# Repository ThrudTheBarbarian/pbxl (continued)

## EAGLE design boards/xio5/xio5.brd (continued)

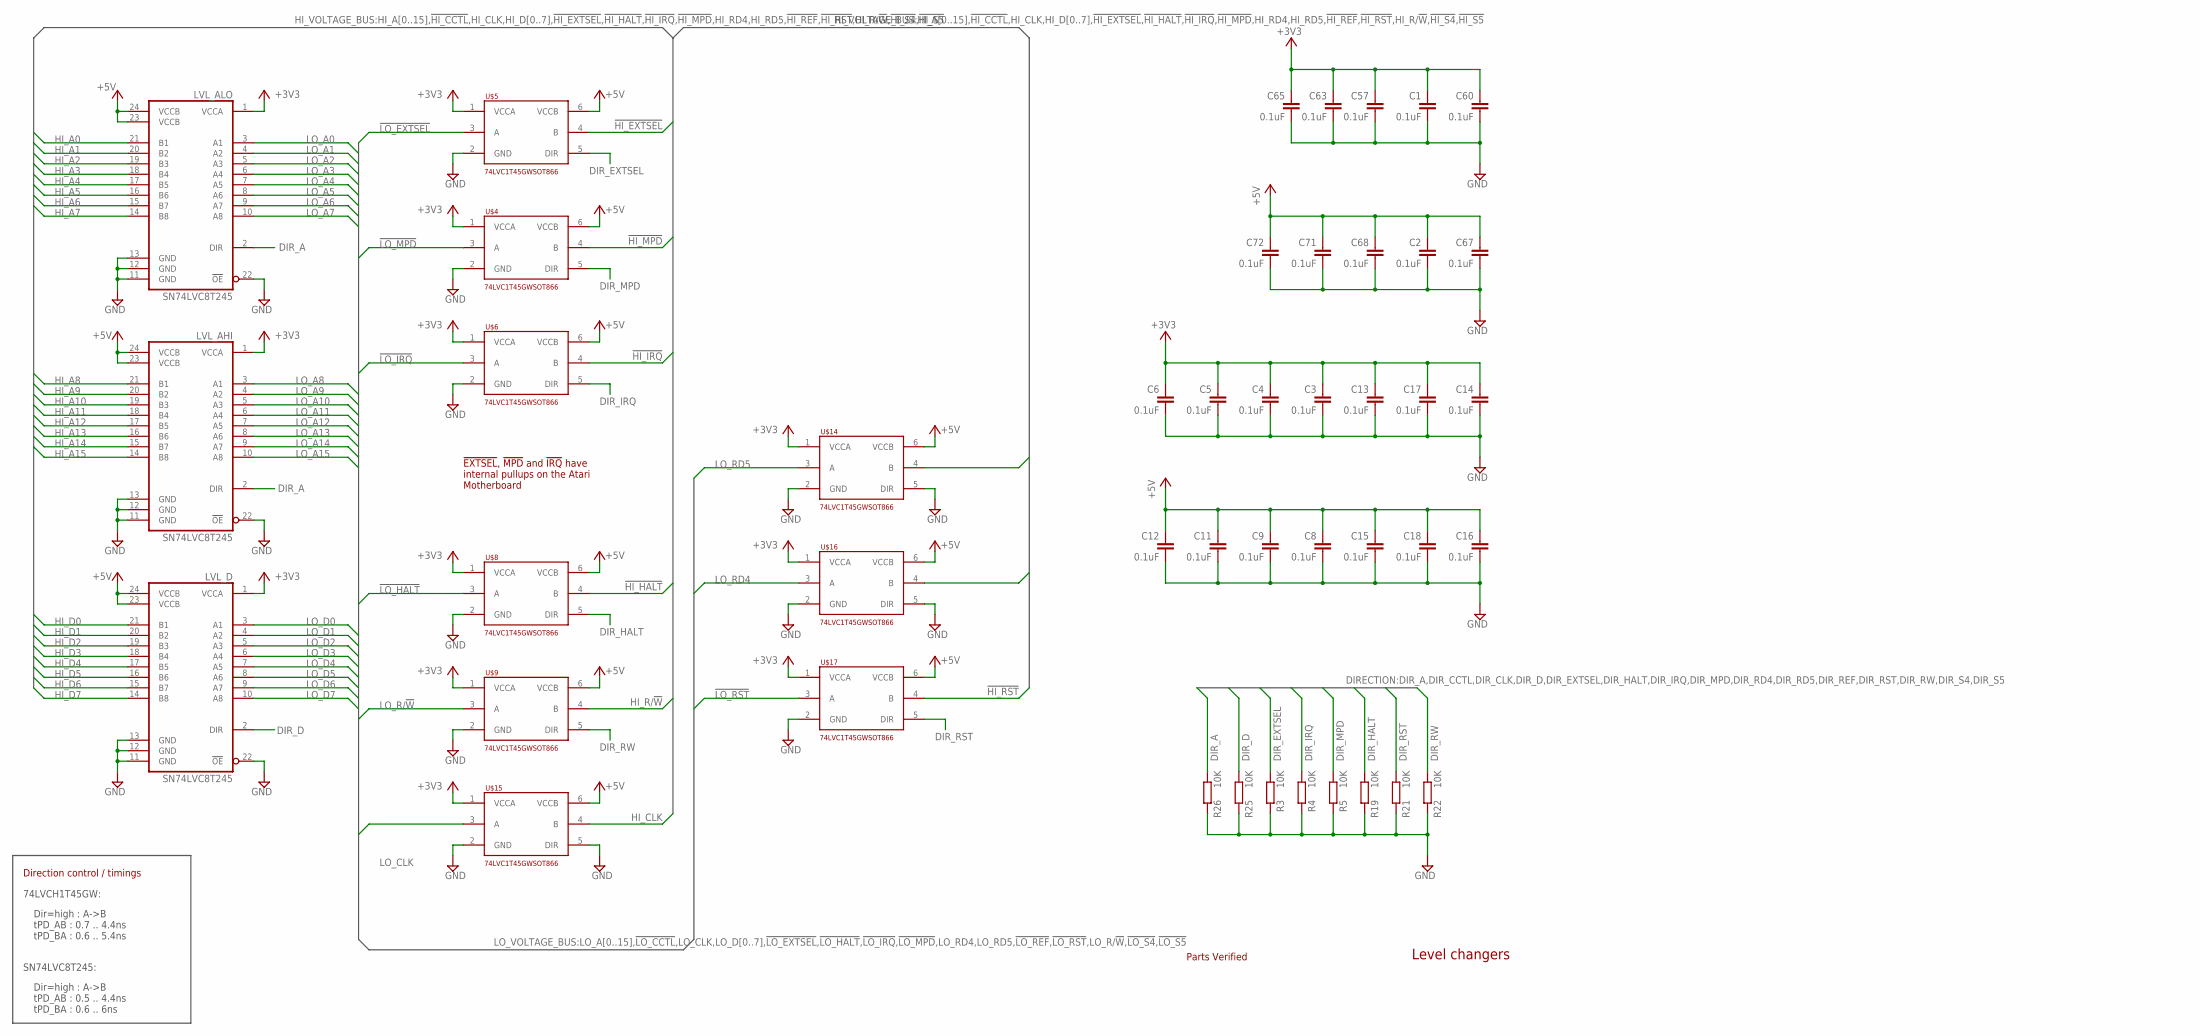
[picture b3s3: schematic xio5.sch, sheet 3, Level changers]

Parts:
C1, C2, C3, C4, C5, C6, C8, C9, C11, C12, C13, C14, C15, C16, C17, C18, C57, C60, C63, C65, C67, C68, C71, C72: 0.1uF; C0201
LVL_AHI: SN74LVC8T245; TSSOP24
LVL_ALO: SN74LVC8T245; TSSOP24
LVL_D: SN74LVC8T245; TSSOP24
R3, R4, R5, R19, R21, R22, R25, R26: 10K; R0201
U$4, U$5, U$6, U$8, U$9, U$14, U$15, U$16, U$17: 74LVC1T45GWSOT866; SOT886

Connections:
!HI_EXTSEL!: U$5.4 (B); also elsewhere on the board
!HI_HALT!: U$8.4 (B); also elsewhere on the board
!HI_IRQ!: U$6.4 (B); also elsewhere on the board
!HI_MPD!: U$4.4 (B); also elsewhere on the board
!HI_RST!: U$17.4 (B); also elsewhere on the board
!LO_EXTSEL!: U$5.3 (A); also elsewhere on the board
!LO_HALT!: U$8.3 (A); also elsewhere on the board
!LO_IRQ!: U$6.3 (A); also elsewhere on the board
!LO_MPD!: U$4.3 (A); also elsewhere on the board
!LO_RST!: U$17.3 (A); also elsewhere on the board
+3V3: C1.1, C3.1, C4.1, C5.1, C6.1, C13.1, C14.1, C17.1, C57.1, C60.1, C63.1, C65.1, LVL_AHI.1 (VCCA), LVL_ALO.1 (VCCA), LVL_D.1 (VCCA), U$4.1 (VCCA), U$5.1 (VCCA), U$6.1 (VCCA), U$8.1 (VCCA), U$9.1 (VCCA), U$14.1 (VCCA), U$15.1 (VCCA), U$16.1 (VCCA), U$17.1 (VCCA); also elsewhere on the board
+5V: C2.1, C8.1, C9.1, C11.1, C12.1, C15.1, C16.1, C18.1, C67.1, C68.1, C71.1, C72.1, LVL_AHI.23 (VCCB), LVL_AHI.24 (VCCB), LVL_ALO.23 (VCCB), LVL_ALO.24 (VCCB), LVL_D.23 (VCCB), LVL_D.24 (VCCB), U$4.6 (VCCB), U$5.6 (VCCB), U$6.6 (VCCB), U$8.6 (VCCB), U$9.6 (VCCB), U$14.6 (VCCB), U$15.6 (VCCB), U$16.6 (VCCB), U$17.6 (VCCB); also elsewhere on the board
DIR_A: LVL_AHI.2 (DIR), LVL_ALO.2 (DIR), R26.1; also elsewhere on the board
DIR_D: LVL_D.2 (DIR), R25.1; also elsewhere on the board
DIR_EXTSEL: R3.1, U$5.5 (DIR); also elsewhere on the board
DIR_HALT: R19.1, U$8.5 (DIR); also elsewhere on the board
DIR_IRQ: R4.1, U$6.5 (DIR); also elsewhere on the board
DIR_MPD: R5.1, U$4.5 (DIR); also elsewhere on the board
DIR_RST: R21.1, U$17.5 (DIR); also elsewhere on the board
DIR_RW: R22.1, U$9.5 (DIR); also elsewhere on the board
GND: C1.2, C2.2, C3.2, C4.2, C5.2, C6.2, C8.2, C9.2, C11.2, C12.2, C13.2, C14.2, C15.2, C16.2, C17.2, C18.2, C57.2, C60.2, C63.2, C65.2, C67.2, C68.2, C71.2, C72.2, LVL_AHI.11 (GND), LVL_AHI.12 (GND), LVL_AHI.13 (GND), LVL_AHI.22 (!OE!), LVL_ALO.11 (GND), LVL_ALO.12 (GND), LVL_ALO.13 (GND), LVL_ALO.22 (!OE!), LVL_D.11 (GND), LVL_D.12 (GND), LVL_D.13 (GND), LVL_D.22 (!OE!), R3.2, R4.2, R5.2, R19.2, R21.2, R22.2, R25.2, R26.2, U$4.2 (GND), U$5.2 (GND), U$6.2 (GND), U$8.2 (GND), U$9.2 (GND), U$14.2 (GND), U$14.5 (DIR), U$15.2 (GND), U$15.5 (DIR), U$16.2 (GND), U$16.5 (DIR), U$17.2 (GND); also elsewhere on the board
HI_A0: LVL_ALO.21 (B1); also elsewhere on the board
HI_A1: LVL_ALO.20 (B2); also elsewhere on the board
HI_A2: LVL_ALO.19 (B3); also elsewhere on the board
HI_A3: LVL_ALO.18 (B4); also elsewhere on the board
HI_A4: LVL_ALO.17 (B5); also elsewhere on the board
HI_A5: LVL_ALO.16 (B6); also elsewhere on the board
HI_A6: LVL_ALO.15 (B7); also elsewhere on the board
HI_A7: LVL_ALO.14 (B8); also elsewhere on the board
HI_A8: LVL_AHI.21 (B1); also elsewhere on the board
HI_A9: LVL_AHI.20 (B2); also elsewhere on the board
HI_A10: LVL_AHI.19 (B3); also elsewhere on the board
HI_A11: LVL_AHI.18 (B4); also elsewhere on the board
HI_A12: LVL_AHI.17 (B5); also elsewhere on the board
HI_A13: LVL_AHI.16 (B6); also elsewhere on the board
HI_A14: LVL_AHI.15 (B7); also elsewhere on the board
HI_A15: LVL_AHI.14 (B8); also elsewhere on the board
HI_CLK: U$15.4 (B); also elsewhere on the board
HI_D0: LVL_D.21 (B1); also elsewhere on the board
HI_D1: LVL_D.20 (B2); also elsewhere on the board
HI_D2: LVL_D.19 (B3); also elsewhere on the board
HI_D3: LVL_D.18 (B4); also elsewhere on the board
HI_D4: LVL_D.17 (B5); also elsewhere on the board
HI_D5: LVL_D.16 (B6); also elsewhere on the board
HI_D6: LVL_D.15 (B7); also elsewhere on the board
HI_D7: LVL_D.14 (B8); also elsewhere on the board
HI_R/!W!: U$9.4 (B); also elsewhere on the board
HI_RD4: U$16.4 (B); also elsewhere on the board
HI_RD5: U$14.4 (B); also elsewhere on the board
LO_A0: LVL_ALO.3 (A1); also elsewhere on the board
LO_A1: LVL_ALO.4 (A2); also elsewhere on the board
LO_A2: LVL_ALO.5 (A3); also elsewhere on the board
LO_A3: LVL_ALO.6 (A4); also elsewhere on the board
LO_A4: LVL_ALO.7 (A5); also elsewhere on the board
LO_A5: LVL_ALO.8 (A6); also elsewhere on the board
LO_A6: LVL_ALO.9 (A7); also elsewhere on the board
LO_A7: LVL_ALO.10 (A8); also elsewhere on the board
LO_A8: LVL_AHI.3 (A1); also elsewhere on the board
LO_A9: LVL_AHI.4 (A2); also elsewhere on the board
LO_A10: LVL_AHI.5 (A3); also elsewhere on the board
LO_A11: LVL_AHI.6 (A4); also elsewhere on the board
LO_A12: LVL_AHI.7 (A5); also elsewhere on the board
LO_A13: LVL_AHI.8 (A6); also elsewhere on the board
LO_A14: LVL_AHI.9 (A7); also elsewhere on the board
LO_A15: LVL_AHI.10 (A8); also elsewhere on the board
LO_CLK: U$15.3 (A); also elsewhere on the board
LO_D0: LVL_D.3 (A1); also elsewhere on the board
LO_D1: LVL_D.4 (A2); also elsewhere on the board
LO_D2: LVL_D.5 (A3); also elsewhere on the board
LO_D3: LVL_D.6 (A4); also elsewhere on the board
LO_D4: LVL_D.7 (A5); also elsewhere on the board
LO_D5: LVL_D.8 (A6); also elsewhere on the board
LO_D6: LVL_D.9 (A7); also elsewhere on the board
LO_D7: LVL_D.10 (A8); also elsewhere on the board
LO_R/!W!: U$9.3 (A); also elsewhere on the board
LO_RD4: U$16.3 (A); also elsewhere on the board
LO_RD5: U$14.3 (A); also elsewhere on the board

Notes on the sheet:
Dir=high : A->B tPD_AB : 0.7 .. 4.4ns tPD_BA : 0.6 .. 5.4ns
74LVCH1T45GW:
SN74LVC8T245:
Dir=high : A->B tPD_AB : 0.5 .. 4.4ns tPD_BA : 0.6 .. 6ns
Direction control / timings
Level changers
!EXTSEL!, !MPD! and !IRQ! have internal pullups on the Atari Motherboard
Parts Verified

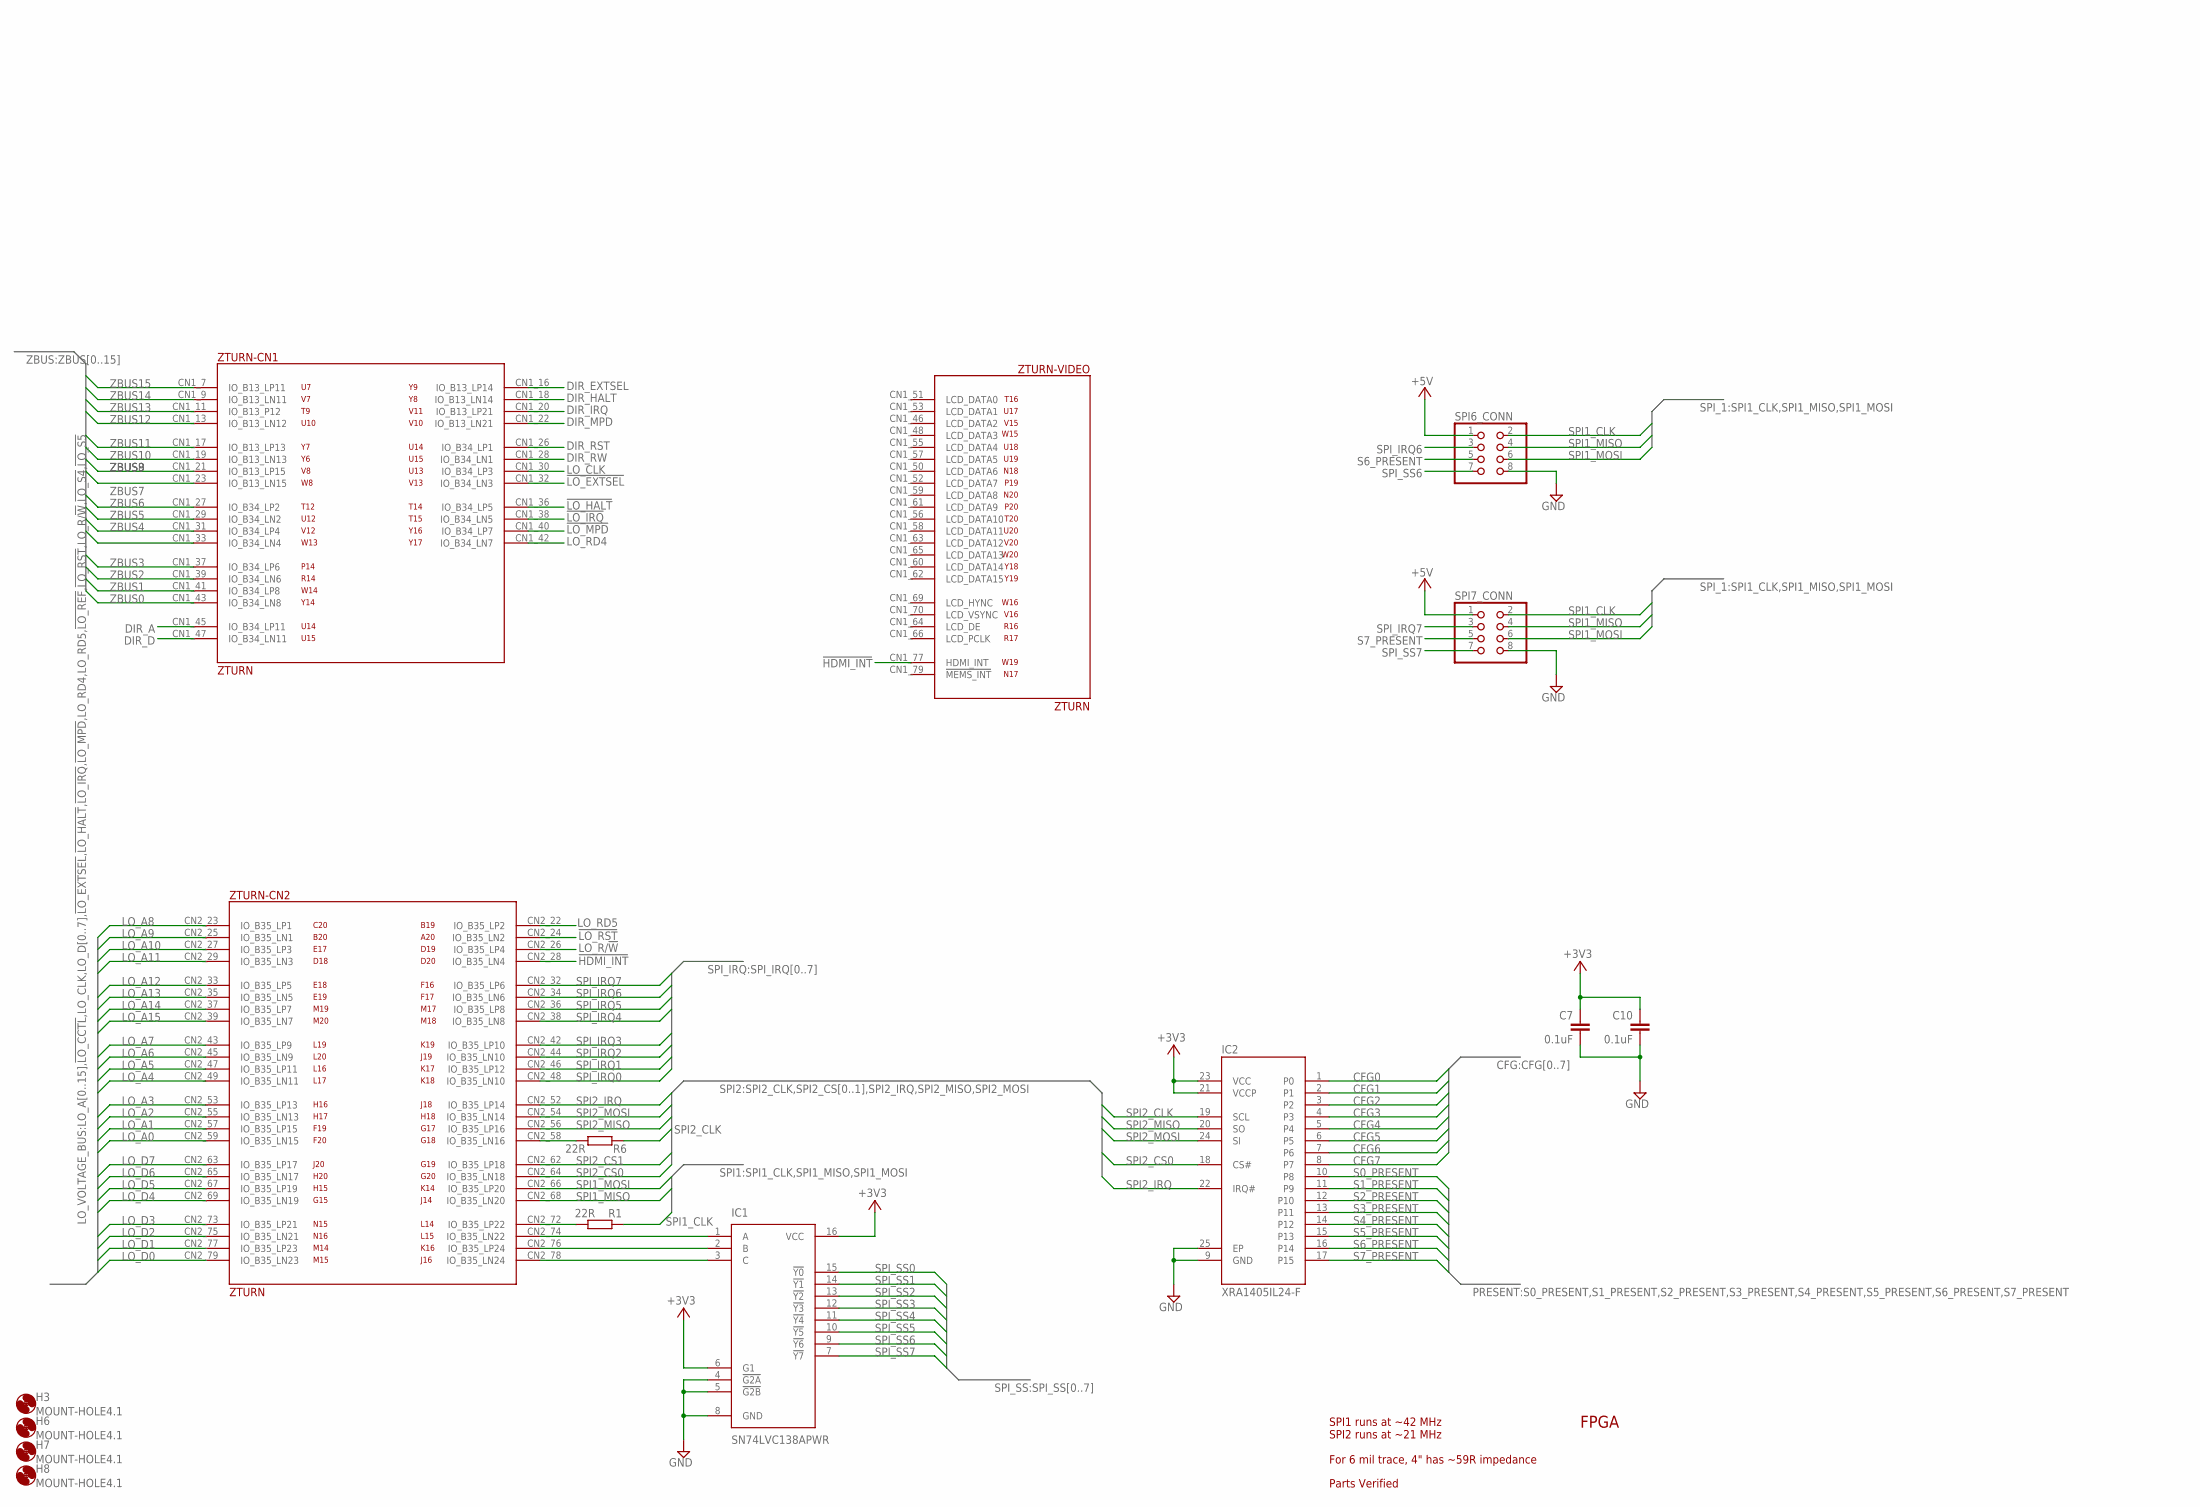
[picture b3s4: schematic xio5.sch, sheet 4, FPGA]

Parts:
C7, C10: 0.1uF; C0201
H3, H6, H7, H8: MOUNT-HOLE4.1; 4,1
IC1: SN74LVC138APWR; SOP65P640X120-16N
IC2: XRA1405IL24-F; QFN50P400X400X100-25N
R1, R6: 22R; R0201
SPI6_CONN, SPI7_CONN: PINHD-2X04_2.00; 2X04M
ZTURN: ZTURN

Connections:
!HDMI_INT!: ZTURN.CN1_77 (HDMI_INT), ZTURN.CN2_28 (IO_B35_LN4)
!LO_EXTSEL!: ZTURN.CN1_32 (IO_B34_LN3); also elsewhere on the board
!LO_HALT!: ZTURN.CN1_36 (IO_B34_LP5); also elsewhere on the board
!LO_IRQ!: ZTURN.CN1_38 (IO_B34_LN5); also elsewhere on the board
!LO_MPD!: ZTURN.CN1_40 (IO_B34_LP7); also elsewhere on the board
!LO_RST!: ZTURN.CN2_24 (IO_B35_LN2); also elsewhere on the board
+3V3: C7.1, C10.1, IC1.6 (G1), IC1.16 (VCC), IC2.21 (VCCP), IC2.23 (VCC); also elsewhere on the board
+5V: SPI6_CONN.1, SPI7_CONN.1; also elsewhere on the board
CFG0: IC2.1 (P0); also elsewhere on the board
CFG1: IC2.2 (P1); also elsewhere on the board
CFG2: IC2.3 (P2); also elsewhere on the board
CFG3: IC2.4 (P3); also elsewhere on the board
CFG4: IC2.5 (P4); also elsewhere on the board
CFG5: IC2.6 (P5); also elsewhere on the board
CFG6: IC2.7 (P6); also elsewhere on the board
CFG7: IC2.8 (P7); also elsewhere on the board
DIR_A: ZTURN.CN1_45 (IO_B34_LP11); also elsewhere on the board
DIR_D: ZTURN.CN1_47 (IO_B34_LN11); also elsewhere on the board
DIR_EXTSEL: ZTURN.CN1_16 (IO_B13_LP14); also elsewhere on the board
DIR_HALT: ZTURN.CN1_18 (IO_B13_LN14); also elsewhere on the board
DIR_IRQ: ZTURN.CN1_20 (IO_B13_LP21); also elsewhere on the board
DIR_MPD: ZTURN.CN1_22 (IO_B13_LN21); also elsewhere on the board
DIR_RST: ZTURN.CN1_26 (IO_B34_LP1); also elsewhere on the board
DIR_RW: ZTURN.CN1_28 (IO_B34_LN1); also elsewhere on the board
GND: C7.2, C10.2, IC1.4 (!G2A), IC1.5 (!G2B), IC1.8 (GND), IC2.9 (GND), IC2.25 (EP), SPI6_CONN.8, SPI7_CONN.8; also elsewhere on the board
LO_A0: ZTURN.CN2_59 (IO_B35_LN15); also elsewhere on the board
LO_A1: ZTURN.CN2_57 (IO_B35_LP15); also elsewhere on the board
LO_A2: ZTURN.CN2_55 (IO_B35_LN13); also elsewhere on the board
LO_A3: ZTURN.CN2_53 (IO_B35_LP13); also elsewhere on the board
LO_A4: ZTURN.CN2_49 (IO_B35_LN11); also elsewhere on the board
LO_A5: ZTURN.CN2_47 (IO_B35_LP11); also elsewhere on the board
LO_A6: ZTURN.CN2_45 (IO_B35_LN9); also elsewhere on the board
LO_A7: ZTURN.CN2_43 (IO_B35_LP9); also elsewhere on the board
LO_A8: ZTURN.CN2_23 (IO_B35_LP1); also elsewhere on the board
LO_A9: ZTURN.CN2_25 (IO_B35_LN1); also elsewhere on the board
LO_A10: ZTURN.CN2_27 (IO_B35_LP3); also elsewhere on the board
LO_A11: ZTURN.CN2_29 (IO_B35_LN3); also elsewhere on the board
LO_A12: ZTURN.CN2_33 (IO_B35_LP5); also elsewhere on the board
LO_A13: ZTURN.CN2_35 (IO_B35_LN5); also elsewhere on the board
LO_A14: ZTURN.CN2_37 (IO_B35_LP7); also elsewhere on the board
LO_A15: ZTURN.CN2_39 (IO_B35_LN7); also elsewhere on the board
LO_CLK: ZTURN.CN1_30 (IO_B34_LP3); also elsewhere on the board
LO_D0: ZTURN.CN2_79 (IO_B35_LN23); also elsewhere on the board
LO_D1: ZTURN.CN2_77 (IO_B35_LP23); also elsewhere on the board
LO_D2: ZTURN.CN2_75 (IO_B35_LN21); also elsewhere on the board
LO_D3: ZTURN.CN2_73 (IO_B35_LP21); also elsewhere on the board
LO_D4: ZTURN.CN2_69 (IO_B35_LN19); also elsewhere on the board
LO_D5: ZTURN.CN2_67 (IO_B35_LP19); also elsewhere on the board
LO_D6: ZTURN.CN2_65 (IO_B35_LN17); also elsewhere on the board
LO_D7: ZTURN.CN2_63 (IO_B35_LP17); also elsewhere on the board
LO_R/!W!: ZTURN.CN2_26 (IO_B35_LP4); also elsewhere on the board
LO_RD4: ZTURN.CN1_42 (IO_B34_LN7); also elsewhere on the board
LO_RD5: ZTURN.CN2_22 (IO_B35_LP2); also elsewhere on the board
unnamed: IC1.1 (A), ZTURN.CN2_74 (IO_B35_LN22)
unnamed: IC1.2 (B), ZTURN.CN2_76 (IO_B35_LP24)
unnamed: IC1.3 (C), ZTURN.CN2_78 (IO_B35_LN24)
unnamed: R1.1, ZTURN.CN2_72 (IO_B35_LP22)
unnamed: R6.1, ZTURN.CN2_58 (IO_B35_LN16)
S0_PRESENT: IC2.10 (P8); also elsewhere on the board
S1_PRESENT: IC2.11 (P9); also elsewhere on the board
S2_PRESENT: IC2.12 (P10); also elsewhere on the board
S3_PRESENT: IC2.13 (P11); also elsewhere on the board
S4_PRESENT: IC2.14 (P12); also elsewhere on the board
S5_PRESENT: IC2.15 (P13); also elsewhere on the board
S6_PRESENT: IC2.16 (P14), SPI6_CONN.5
S7_PRESENT: IC2.17 (P15), SPI7_CONN.5
SPI1_CLK: R1.2, SPI6_CONN.2, SPI7_CONN.2; also elsewhere on the board
SPI1_MISO: SPI6_CONN.4, SPI7_CONN.4, ZTURN.CN2_68 (IO_B35_LN20); also elsewhere on the board
SPI1_MOSI: SPI6_CONN.6, SPI7_CONN.6, ZTURN.CN2_66 (IO_B35_LP20); also elsewhere on the board
SPI2_CLK: IC2.19 (SCL), R6.2; also elsewhere on the board
SPI2_CS0: IC2.18 (CS#), ZTURN.CN2_64 (IO_B35_LN18)
SPI2_CS1: ZTURN.CN2_62 (IO_B35_LP18); also elsewhere on the board
SPI2_IRQ: IC2.22 (IRQ#), ZTURN.CN2_52 (IO_B35_LP14); also elsewhere on the board
SPI2_MISO: IC2.20 (SO), ZTURN.CN2_56 (IO_B35_LP16); also elsewhere on the board
SPI2_MOSI: IC2.24 (SI), ZTURN.CN2_54 (IO_B35_LN14); also elsewhere on the board
SPI_IRQ0: ZTURN.CN2_48 (IO_B35_LN10); also elsewhere on the board
SPI_IRQ1: ZTURN.CN2_46 (IO_B35_LP12); also elsewhere on the board
SPI_IRQ2: ZTURN.CN2_44 (IO_B35_LN10); also elsewhere on the board
SPI_IRQ3: ZTURN.CN2_42 (IO_B35_LP10); also elsewhere on the board
SPI_IRQ4: ZTURN.CN2_38 (IO_B35_LN8); also elsewhere on the board
SPI_IRQ5: ZTURN.CN2_36 (IO_B35_LP8); also elsewhere on the board
SPI_IRQ6: SPI6_CONN.3, ZTURN.CN2_34 (IO_B35_LN6)
SPI_IRQ7: SPI7_CONN.3, ZTURN.CN2_32 (IO_B35_LP6)
SPI_SS0: IC1.15 (!Y0); also elsewhere on the board
SPI_SS1: IC1.14 (!Y1); also elsewhere on the board
SPI_SS2: IC1.13 (!Y2); also elsewhere on the board
SPI_SS3: IC1.12 (!Y3); also elsewhere on the board
SPI_SS4: IC1.11 (!Y4); also elsewhere on the board
SPI_SS5: IC1.10 (!Y5); also elsewhere on the board
SPI_SS6: IC1.9 (!Y6), SPI6_CONN.7
SPI_SS7: IC1.7 (!Y7), SPI7_CONN.7
ZBUS0: ZTURN.CN1_43 (IO_B34_LN8); also elsewhere on the board
ZBUS1: ZTURN.CN1_41 (IO_B34_LP8); also elsewhere on the board
ZBUS2: ZTURN.CN1_39 (IO_B34_LN6); also elsewhere on the board
ZBUS3: ZTURN.CN1_37 (IO_B34_LP6); also elsewhere on the board
ZBUS4: ZTURN.CN1_33 (IO_B34_LN4); also elsewhere on the board
ZBUS5: ZTURN.CN1_31 (IO_B34_LP4); also elsewhere on the board
ZBUS6: ZTURN.CN1_29 (IO_B34_LN2); also elsewhere on the board
ZBUS7: ZTURN.CN1_27 (IO_B34_LP2); also elsewhere on the board
ZBUS8: ZTURN.CN1_23 (IO_B13_LN15); also elsewhere on the board
ZBUS9: ZTURN.CN1_21 (IO_B13_LP15); also elsewhere on the board
ZBUS10: ZTURN.CN1_19 (IO_B13_LN13); also elsewhere on the board
ZBUS11: ZTURN.CN1_17 (IO_B13_LP13); also elsewhere on the board
ZBUS12: ZTURN.CN1_13 (IO_B13_LN12); also elsewhere on the board
ZBUS13: ZTURN.CN1_11 (IO_B13_P12); also elsewhere on the board
ZBUS14: ZTURN.CN1_9 (IO_B13_LN11); also elsewhere on the board
ZBUS15: ZTURN.CN1_7 (IO_B13_LP11); also elsewhere on the board

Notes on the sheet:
FPGA
SPI1 runs at ~42 MHz SPI2 runs at ~21 MHz For 6 mil trace, 4" has ~59R impedance
Parts Verified

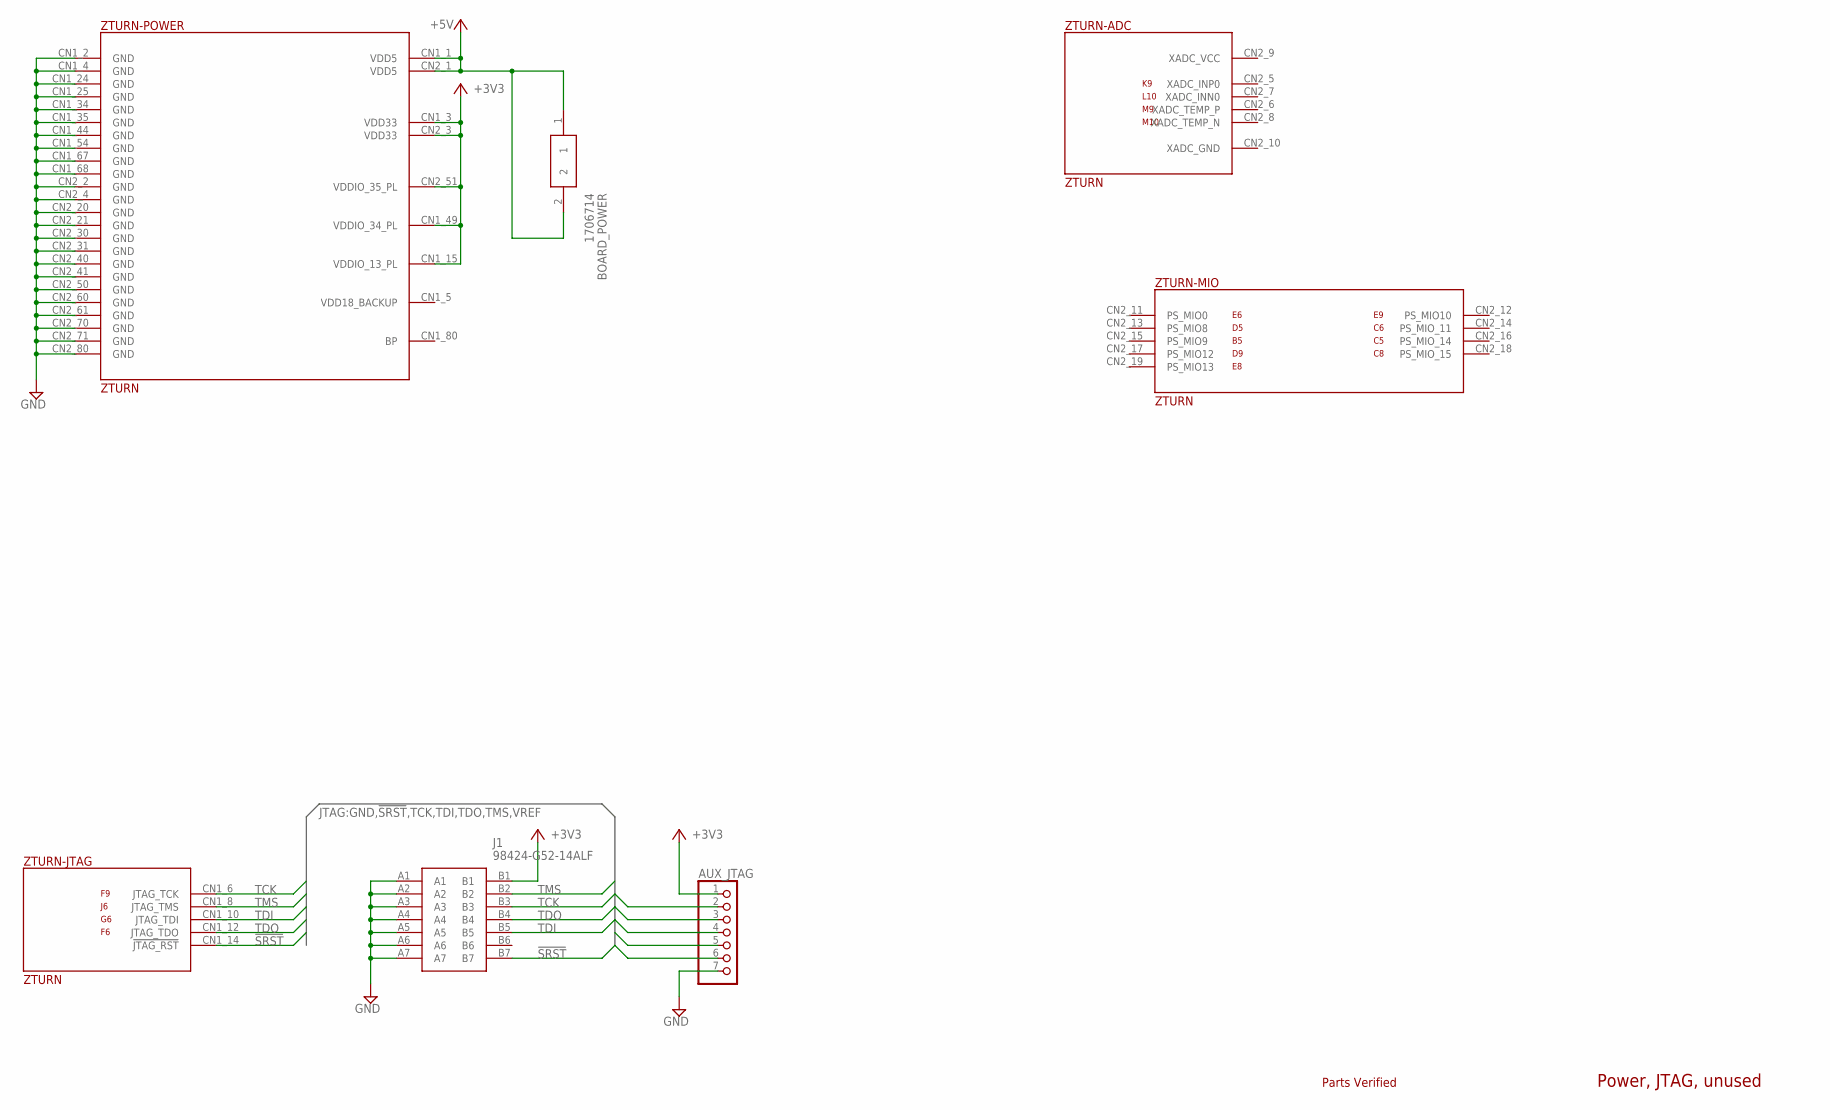
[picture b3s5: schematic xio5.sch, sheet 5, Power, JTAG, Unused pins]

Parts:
AUX_JTAG: PINHD-1X7; 1X07
BOARD_POWER: 1706714
J1: 98424-G52-14ALF; 98424G5214ALF
ZTURN: ZTURN

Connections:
!SRST!: AUX_JTAG.6, J1.B7, ZTURN.CN1_14 (!JTAG_RST!)
+3V3: AUX_JTAG.1, J1.B1, ZTURN.CN1_3 (VDD33), ZTURN.CN1_15 (VDDIO_13_PL), ZTURN.CN1_49 (VDDIO_34_PL), ZTURN.CN2_3 (VDD33), ZTURN.CN2_51 (VDDIO_35_PL); also elsewhere on the board
+5V: BOARD_POWER.1, BOARD_POWER.2, ZTURN.CN1_1 (VDD5), ZTURN.CN2_1 (VDD5); also elsewhere on the board
GND: AUX_JTAG.7, J1.A1, J1.A2, J1.A3, J1.A4, J1.A5, J1.A6, J1.A7, ZTURN.CN1_2 (GND), ZTURN.CN1_4 (GND), ZTURN.CN1_24 (GND), ZTURN.CN1_25 (GND), ZTURN.CN1_34 (GND), ZTURN.CN1_35 (GND), ZTURN.CN1_44 (GND), ZTURN.CN1_54 (GND), ZTURN.CN1_67 (GND), ZTURN.CN1_68 (GND), ZTURN.CN2_2 (GND), ZTURN.CN2_4 (GND), ZTURN.CN2_20 (GND), ZTURN.CN2_21 (GND), ZTURN.CN2_30 (GND), ZTURN.CN2_31 (GND), ZTURN.CN2_40 (GND), ZTURN.CN2_41 (GND), ZTURN.CN2_50 (GND), ZTURN.CN2_60 (GND), ZTURN.CN2_61 (GND), ZTURN.CN2_70 (GND), ZTURN.CN2_71 (GND), ZTURN.CN2_80 (GND); also elsewhere on the board
TCK: AUX_JTAG.3, J1.B3, ZTURN.CN1_6 (JTAG_TCK)
TDI: AUX_JTAG.5, J1.B5, ZTURN.CN1_10 (JTAG_TDI)
TDO: AUX_JTAG.4, J1.B4, ZTURN.CN1_12 (JTAG_TDO)
TMS: AUX_JTAG.2, J1.B2, ZTURN.CN1_8 (JTAG_TMS)

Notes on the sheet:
Power, JTAG, unused
Parts Verified

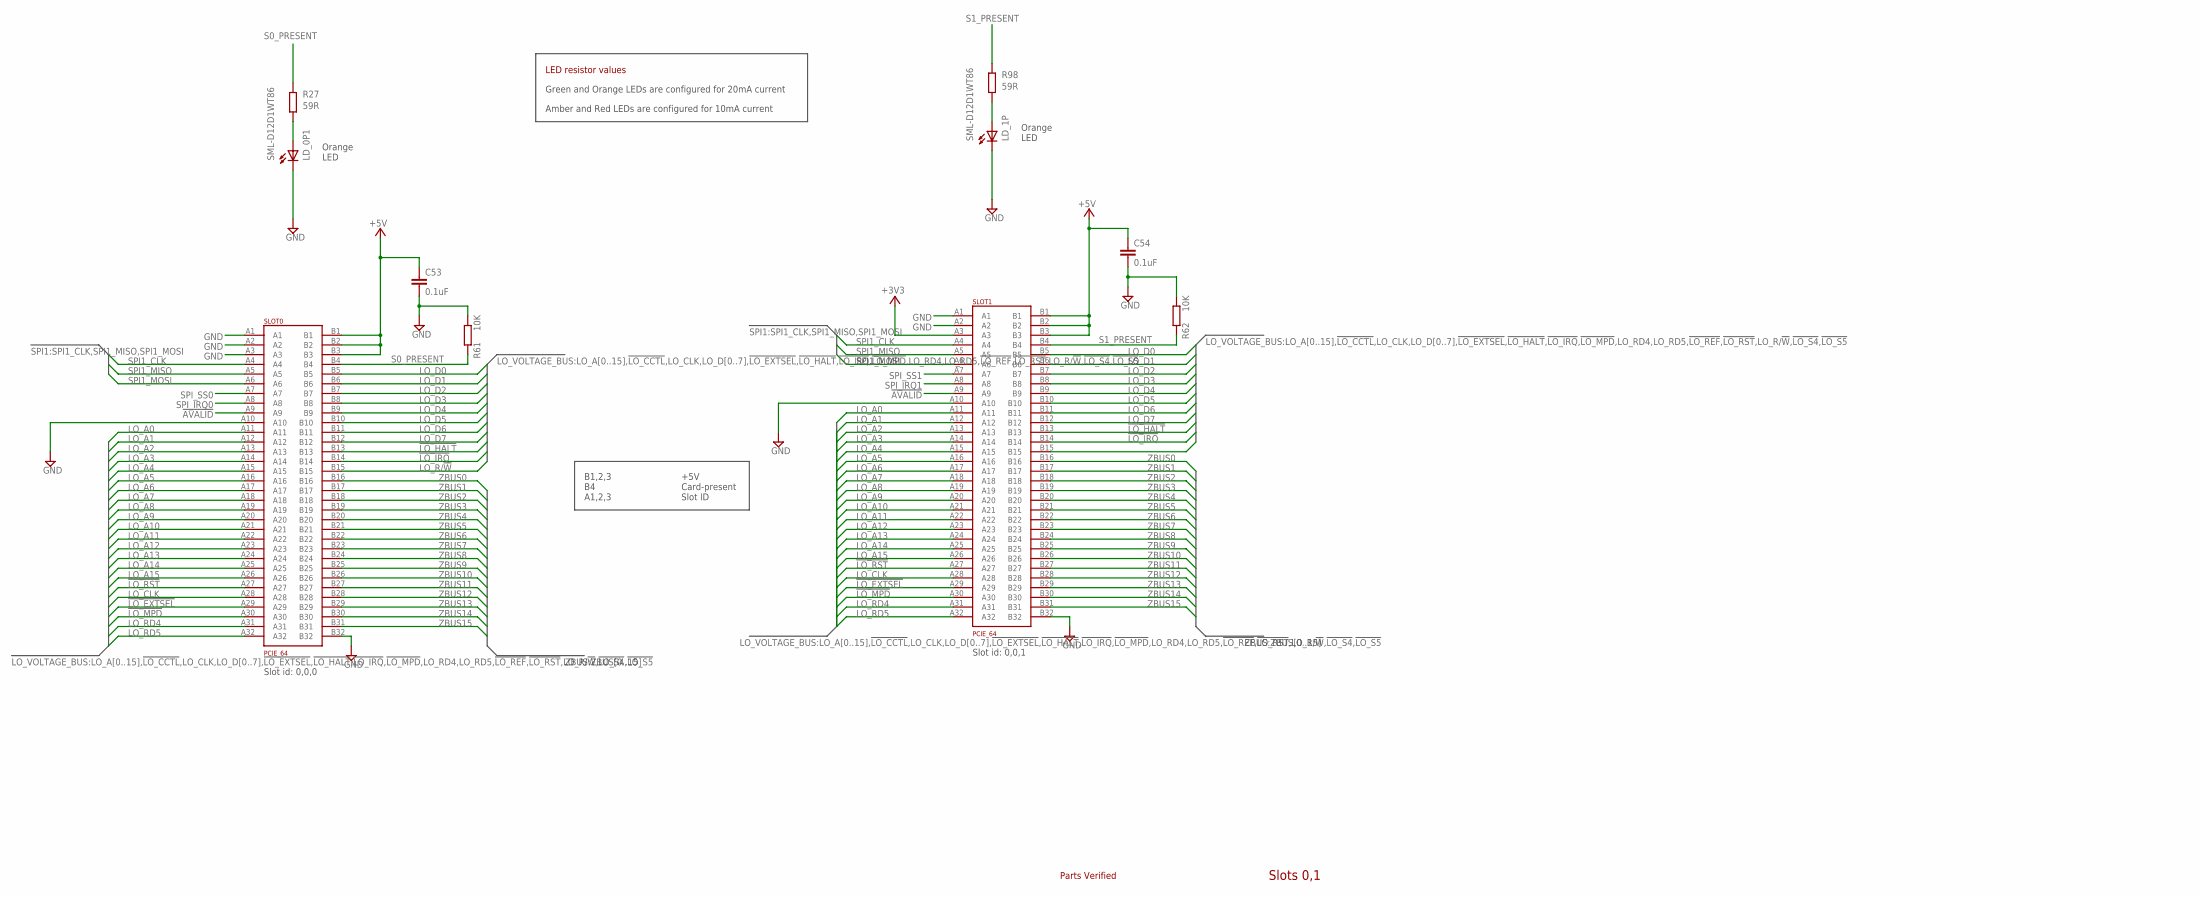
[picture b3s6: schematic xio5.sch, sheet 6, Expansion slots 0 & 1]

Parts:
C53, C54: 0.1uF; C0201
LD_0P1, LD_1P: SML-D12D1WT86; CHIPLED_0603
R27, R98: 59R; R0402
R61, R62: 10K; R0201
SLOT0, SLOT1: PCIE_64; PCI-E_64

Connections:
!AVALID!: SLOT0.A9, SLOT1.A9; also elsewhere on the board
!LO_EXTSEL!: SLOT0.A29, SLOT1.A29; also elsewhere on the board
!LO_HALT!: SLOT0.B13, SLOT1.B13; also elsewhere on the board
!LO_IRQ!: SLOT0.B14, SLOT1.B14; also elsewhere on the board
!LO_MPD!: SLOT0.A30, SLOT1.A30; also elsewhere on the board
!LO_RST!: SLOT0.A27, SLOT1.A27; also elsewhere on the board
+3V3: SLOT1.A3; also elsewhere on the board
+5V: C53.1, C54.1, SLOT0.B1, SLOT0.B2, SLOT0.B3, SLOT1.B1, SLOT1.B2, SLOT1.B3; also elsewhere on the board
GND: C53.2, C54.2, LD_0P1.C, LD_1P.C, R61.1, R62.1, SLOT0.A1, SLOT0.A2, SLOT0.A3, SLOT0.A10, SLOT0.B32, SLOT1.A1, SLOT1.A2, SLOT1.A10, SLOT1.B32; also elsewhere on the board
LO_A0: SLOT0.A11, SLOT1.A11; also elsewhere on the board
LO_A1: SLOT0.A12, SLOT1.A12; also elsewhere on the board
LO_A2: SLOT0.A13, SLOT1.A13; also elsewhere on the board
LO_A3: SLOT0.A14, SLOT1.A14; also elsewhere on the board
LO_A4: SLOT0.A15, SLOT1.A15; also elsewhere on the board
LO_A5: SLOT0.A16, SLOT1.A16; also elsewhere on the board
LO_A6: SLOT0.A17, SLOT1.A17; also elsewhere on the board
LO_A7: SLOT0.A18, SLOT1.A18; also elsewhere on the board
LO_A8: SLOT0.A19, SLOT1.A19; also elsewhere on the board
LO_A9: SLOT0.A20, SLOT1.A20; also elsewhere on the board
LO_A10: SLOT0.A21, SLOT1.A21; also elsewhere on the board
LO_A11: SLOT0.A22, SLOT1.A22; also elsewhere on the board
LO_A12: SLOT0.A23, SLOT1.A23; also elsewhere on the board
LO_A13: SLOT0.A24, SLOT1.A24; also elsewhere on the board
LO_A14: SLOT0.A25, SLOT1.A25; also elsewhere on the board
LO_A15: SLOT0.A26, SLOT1.A26; also elsewhere on the board
LO_CLK: SLOT0.A28, SLOT1.A28; also elsewhere on the board
LO_D0: SLOT0.B5, SLOT1.B5; also elsewhere on the board
LO_D1: SLOT0.B6, SLOT1.B6; also elsewhere on the board
LO_D2: SLOT0.B7, SLOT1.B7; also elsewhere on the board
LO_D3: SLOT0.B8, SLOT1.B8; also elsewhere on the board
LO_D4: SLOT0.B9, SLOT1.B9; also elsewhere on the board
LO_D5: SLOT0.B10, SLOT1.B10; also elsewhere on the board
LO_D6: SLOT0.B11, SLOT1.B11; also elsewhere on the board
LO_D7: SLOT0.B12, SLOT1.B12; also elsewhere on the board
LO_R/!W!: SLOT0.B15, SLOT1.B15; also elsewhere on the board
LO_RD4: SLOT0.A31, SLOT1.A31; also elsewhere on the board
LO_RD5: SLOT0.A32, SLOT1.A32; also elsewhere on the board
unnamed: LD_0P1.A, R27.2
unnamed: LD_1P.A, R98.2
S0_PRESENT: R27.1, R61.2, SLOT0.B4; also elsewhere on the board
S1_PRESENT: R62.2, R98.1, SLOT1.B4; also elsewhere on the board
SPI1_CLK: SLOT0.A4, SLOT1.A4; also elsewhere on the board
SPI1_MISO: SLOT0.A5, SLOT1.A5; also elsewhere on the board
SPI1_MOSI: SLOT0.A6, SLOT1.A6; also elsewhere on the board
SPI_IRQ0: SLOT0.A8; also elsewhere on the board
SPI_IRQ1: SLOT1.A8; also elsewhere on the board
SPI_SS0: SLOT0.A7; also elsewhere on the board
SPI_SS1: SLOT1.A7; also elsewhere on the board
ZBUS0: SLOT0.B16, SLOT1.B16; also elsewhere on the board
ZBUS1: SLOT0.B17, SLOT1.B17; also elsewhere on the board
ZBUS2: SLOT0.B18, SLOT1.B18; also elsewhere on the board
ZBUS3: SLOT0.B19, SLOT1.B19; also elsewhere on the board
ZBUS4: SLOT0.B20, SLOT1.B20; also elsewhere on the board
ZBUS5: SLOT0.B21, SLOT1.B21; also elsewhere on the board
ZBUS6: SLOT0.B22, SLOT1.B22; also elsewhere on the board
ZBUS7: SLOT0.B23, SLOT1.B23; also elsewhere on the board
ZBUS8: SLOT0.B24, SLOT1.B24; also elsewhere on the board
ZBUS9: SLOT0.B25, SLOT1.B25; also elsewhere on the board
ZBUS10: SLOT0.B26, SLOT1.B26; also elsewhere on the board
ZBUS11: SLOT0.B27, SLOT1.B27; also elsewhere on the board
ZBUS12: SLOT0.B28, SLOT1.B28; also elsewhere on the board
ZBUS13: SLOT0.B29, SLOT1.B29; also elsewhere on the board
ZBUS14: SLOT0.B30, SLOT1.B30; also elsewhere on the board
ZBUS15: SLOT0.B31, SLOT1.B31; also elsewhere on the board

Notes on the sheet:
Slots 0,1
Slot id: 0,0,0
Slot id: 0,0,1
B1,2,3 B4 A1,2,3
+5V Card-present Slot ID
Orange LED
Green and Orange LEDs are configured for 20mA current
Amber and Red LEDs are configured for 10mA current
LED resistor values
Parts Verified
